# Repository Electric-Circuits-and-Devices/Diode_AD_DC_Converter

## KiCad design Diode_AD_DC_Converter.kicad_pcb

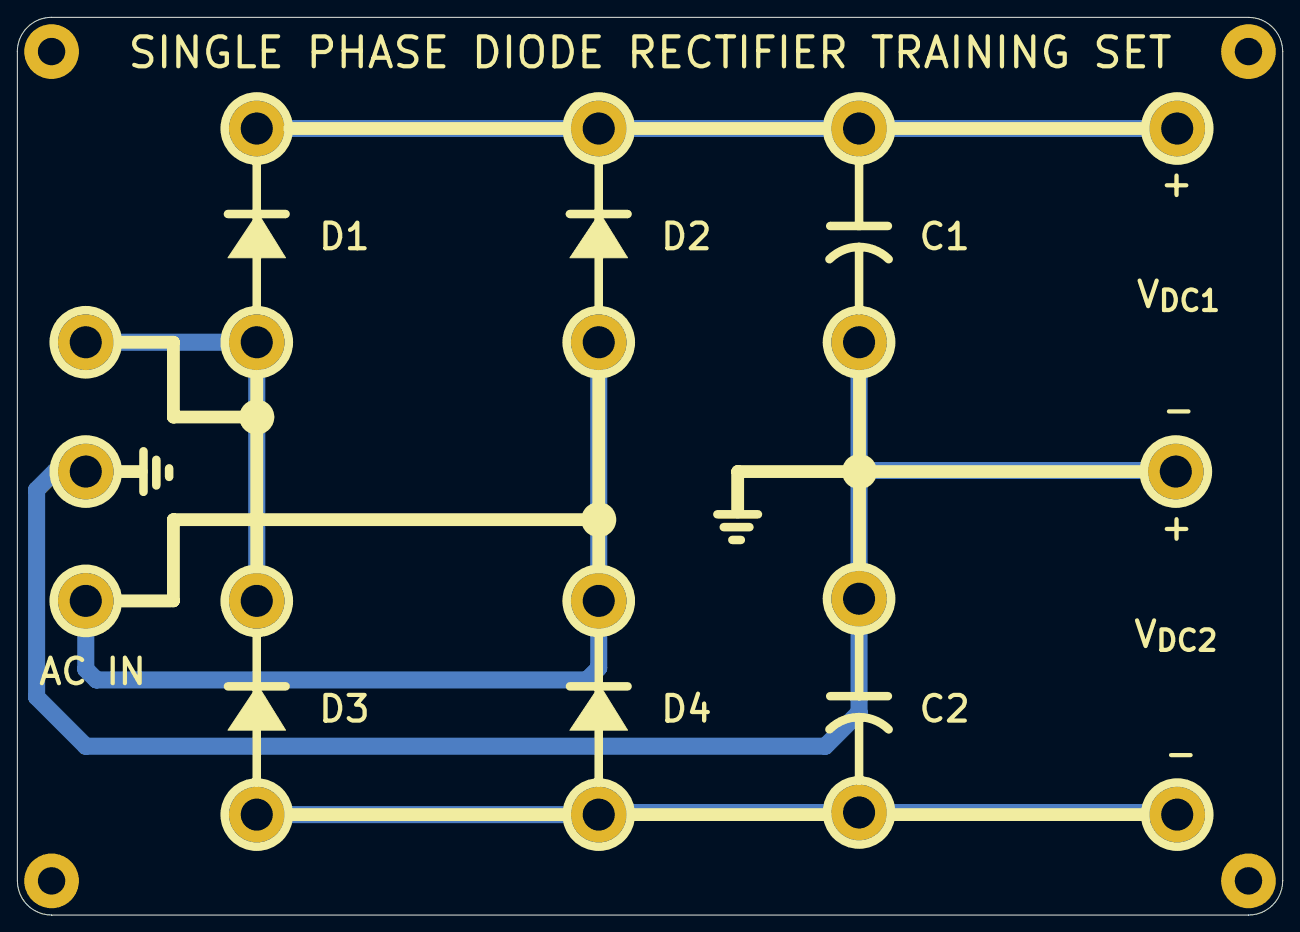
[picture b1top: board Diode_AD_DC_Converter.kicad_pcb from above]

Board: 2 copper layers, 148.0 x 105.0 mm, 16 parts (0 on the bottom side), 5 nets.

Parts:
C5, C6: C_Small; Capacitor-Plugin_Electrolyte
D1, D2, D3, D4: D; Diode-Plugin
H1, H2, H3, H4: MountingHole; MountingHole_3.2mm_M3_Pad
J1, J2, J3, J4, J5, J6: Conn_01x01_Pin; Banana_2mm

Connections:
GND: C5.2, C6.1, J5.1, J6.1
unnamed: D1.2 (A), D3.1 (K), J1.1
unnamed: C5.1, D1.1 (K), D2.1 (K), J3.1
unnamed: D2.2 (A), D4.1 (K), J2.1
unnamed: C6.2, D3.2 (A), D4.2 (A), J4.1
